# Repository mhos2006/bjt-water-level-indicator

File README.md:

# BJT Water Level Indicator

## Overview

A water level indicator using NPN BJTs forced into saturation mode via a minuscule current from tap water, which flows into the base and is amplified to light up a reference LED.

## Hardware Specifications

- **Level Indicators** 3× LEDs
- **Current Amplifier** 3× 2N3904 BJTs
- **Probes** 4× 15+cm 22 AWG stripped wire (1× Master Probe, 3× Probes connected to base of 2N3904 BJTs)
- **Circuit Protection** 3× 1kΩ Resistors

## Prerequisites

To achieve my 5V power rail, I used a battery pack regulated to output 5V. Here is a link to the repository:
[5V Linear Breadboard Power Supply](https://github.com/mhos2006/starter-dc-makeshift-power-supply)

## Schematic

## Testing

https://github.com/user-attachments/assets/e5b6b6be-7824-49d6-9163-9148845a0b6e

## Schematic and PCB Documentation

I created the schematic using KiCad software. While my schematic has been verified, I have moved the components over to PCB software. PCB layout and component placement is in progress.

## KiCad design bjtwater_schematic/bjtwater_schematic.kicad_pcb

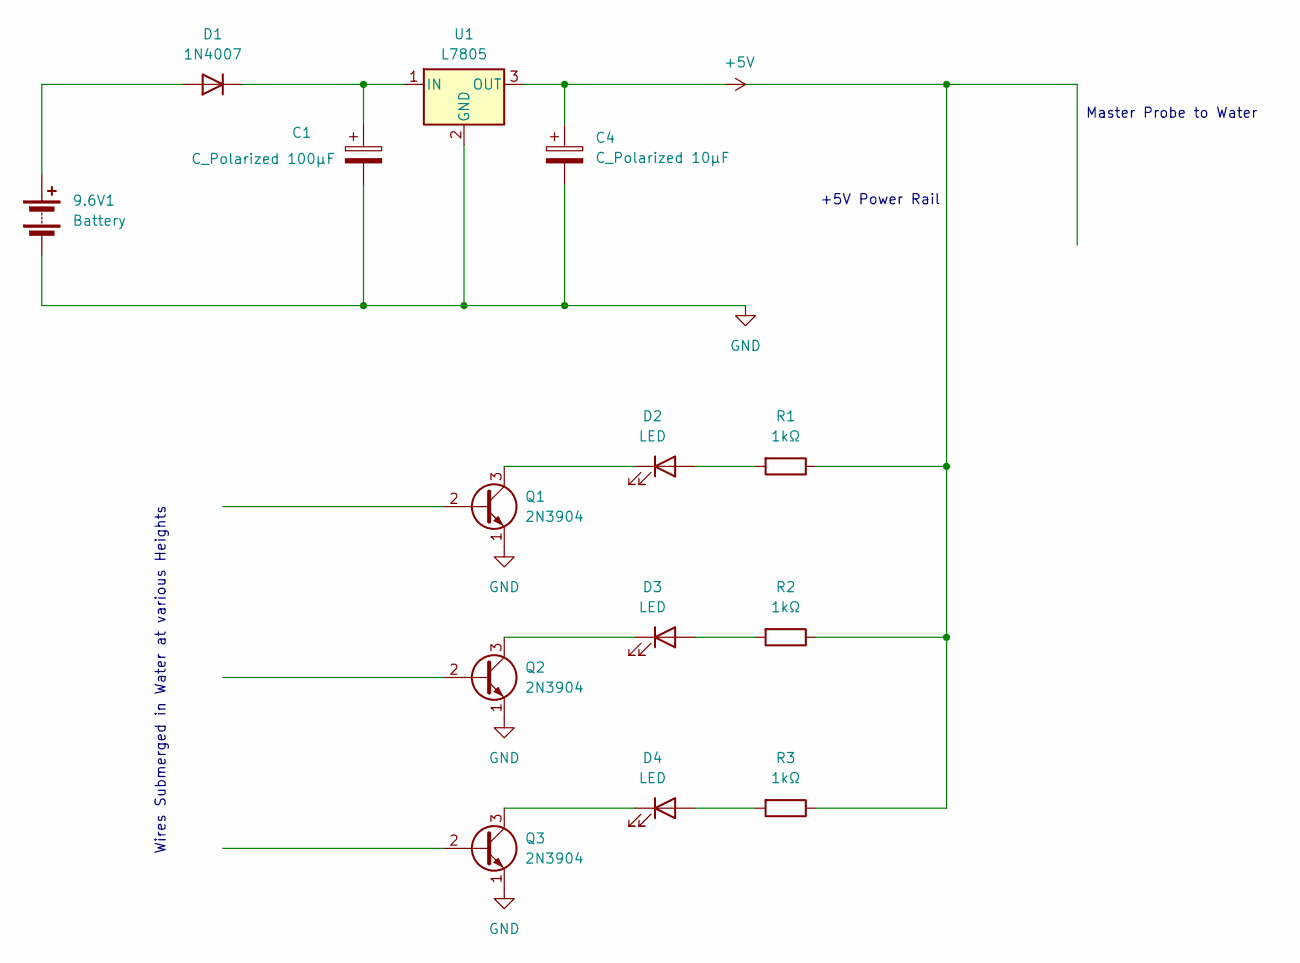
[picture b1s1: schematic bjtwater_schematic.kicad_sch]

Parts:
9.6V1: Battery; PinHeader_1x02_P2.54mm_Vertical
C1: C_Polarized 100μF; CP_Radial_D5.0mm_P2.00mm
C4: C_Polarized 10μF; CP_Radial_D5.0mm_P2.00mm
D1: 1N4007; D_DO-41_SOD81_P10.16mm_Horizontal
D2, D3, D4: LED; D_DO-41_SOD81_P10.16mm_Horizontal
Q1, Q2, Q3: 2N3904; TO-92_Inline
R1, R2, R3: 1kΩ; R_Axial_DIN0207_L6.3mm_D2.5mm_P10.16mm_Horizontal
U1: L7805; TO-220-3_Vertical

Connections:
+5V: C4.1, U1.3 (OUT)
GND: 9.6V1.2 (-), C1.2, C4.2, Q1.1 (E), Q2.1 (E), Q3.1 (E), U1.2 (GND)
unnamed: 9.6V1.1 (+), D1.2 (A)
unnamed: C1.1, D1.1 (K), U1.1 (IN)
unnamed: D2.2 (A), R1.2
unnamed: D2.1 (K), Q1.3 (C)
unnamed: D3.2 (A), R2.2
unnamed: D3.1 (K), Q2.3 (C)
unnamed: D4.2 (A), R3.2
unnamed: D4.1 (K), Q3.3 (C)
unnamed: R1.1, R2.1, R3.1

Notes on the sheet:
Wires Submerged in Water at various Heights
Master Probe to Water
+5V Power Rail

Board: 2 copper layers, 14 parts (0 on the bottom side), 11 nets, no tracks yet.
